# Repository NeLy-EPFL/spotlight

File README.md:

# Spotlight controller

This repository contains the control software for the Spotlight system presented in [Wang-Chen et al. (2026), Precise kinematic and muscle recording in freely behaving flies enabled by closed-loop tracking and annotation-free pose estimation
](https://go.epfl.ch/spotlight-poseforge). The firmware for the triggering microcontroller is also included.

The closed-loop control and recording programs implemented in C++. A set of offline tools for calibration, postprocessing, etc. is implemented in Python and lives in [`tools/`](tools/). The C++ codebase contains three parts:

- **`recorder/`:** The main recorder software that runs on the recording computer.
    - User-facing programs: `align-cameras`, `run-arena-registration-scan`, `run-spotlight`, and `run-homography-scan` _(planned; not yet implemented — see [`docs/configuration/camera_homography.md`](docs/configuration/camera_homography.md))_.
        - `align-cameras`: (i) _mechanically_ align the two cameras and the blue excitation light, and (ii) define a cropped ROI on each of the two muscle cameras to align the fields of view.
        - `run-arena-registration-scan`: move the translation stages to predefined positions and capture fiducial-marker snapshots, used by a Python tool to build a camera–stage–arena coordinate mapping.
        - `run-spotlight`: the main program to record experimental data.
        - `run-spotlight-headless`: `run-spotlight` without the GUI, for automated testing and performance analysis.
    - The behavior (Euresys) camera runs in-process; the two muscle (PCO) cameras run in one separate process (`pco-camera-server`) communicating over shared memory. See [`docs/architecture.md`](docs/architecture.md) for details.
- **`trigger_firmware/`**: The embedded code that runs on the triggering microcontroller.
- **`comm_protocol/`**: A lightweight JSON-based library for serial communication between the recorder and the microcontroller. Designed to be included by both sides; avoids exceptions to respect the microcontroller's linear workflow.

The repository also contains:

- **`tools/`**: Offline Python tools for calibration and postprocessing (`fit-arena-registration`, `postprocess-recording`, etc.). See `tools/README.md`.
- **`trigger_hardware/`**: KiCad schematic and PCB layout for the triggering microcontroller circuit board.

## Documentation & developer info

Documentation is available in the `docs/` folder. Start at the index,
[`docs/README.md`](docs/README.md), which splits the pages into a short **User's
manual** (running an experiment end to end) and a fuller **Developer's manual**
(internals, environment setup, hardware). A few entry points:

- [Architecture overview](docs/architecture.md): threads, cameras, and the trigger microcontroller.
- [Data acquisition workflow](docs/data_acquisition.md): how the cameras and lights are controlled and synchronized using continuous acquisition.
- [Building and installing](docs/setup/building.md) and [software dependencies](docs/setup/dependencies.md): how to build the components and install their dependencies.
- [Troubleshooting](docs/troubleshooting.md): common runtime problems (e.g. the behavior camera grabber being held by another program, and hangs on quit).

- Code style and conventions (language standards, formatting, naming, overhead, tests)
are documented in [`docs/code_style.md`](docs/code_style.md).

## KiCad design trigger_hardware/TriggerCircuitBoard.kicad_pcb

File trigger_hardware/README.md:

# Trigger circuit hardware

This folder contains the hardware design of the trigger controller.

See `TriggerCircuitBoard.pdf` for a schematic diagram of the triggering circuit. The CAD files (`.kicad_pro`, `.kicad_sch`, `.kicad_pcb`) can be opened using [KiCAD](https://www.kicad.org/).

## Bill of materials

Note: Symbols are as shown in the schematic diagram. All components are through-hole-mounted (THT), 2.54 mm pitch. Components can generally be replaced by equivalent parts. Exception: replacement of the microcontroller and the status display is possible but requires firmware code change.

| Symbol | Description | Model |
| --- | --- | --- |
| A1 | Microcontroller | Arduino Nano ESP32 |
| Q1–3 | NPN BJT transistors | Onsemi BC33725BU |
| R1–3 | ~500 Ω resistors | Vishay MBB02070C5600FCT00 |
| R4–6 | ~1 kΩ resistors | Vishay MRS16000C1001FC100 |
| D1 | RGB LED | RND 135-00191 |
| DISP1 | Display with I2C backpack | Midas MDOB128064WV-YBI |
| C1 | Polarized capacitor, ~200 μF, ≥ 24 V | Würth Elektronik 860010473011
| C2 | Non-polarized capacitor, ~100 nF, ≥ 3.3 V | Kemet μ1J63 1M2 |
| SW1 | Double pole, single throw (DPST) switch | RND 210-00549 |
| SW2 | Pushbutton | RND 210-00577 |
| J1–2 | Header pins & receptacles | Preci-Dip 890-18-036-10-804 / 3 (pins, soldered on Arduino) & 801-87-050-10-001101 (receptacles, soldered on PCB)
| J3 | 10-contact IDC connectors & cable | RS PRO 625-7252 plug (soldered on PCB), Würth Elektronik 63911015521CAB ribbon cable with RND 205-00682 socket (PCB side) and 3M 7100234235 panel-mount socket (on the exterior of the electronics box)
| J4 | 2-contact screw terminal & DC pwer connector | Phoenix Contact 2204260 screw terminal & RND 205-00909 external DC power connector |
| J5–10 | 4-contact screw terminal | Phoenix Contact 1725672 |
| J11–14 | BNC RF socket | RS PRO 546-3995 |

Additionally: Various jump wires, prototyping PCB (RS PRO 159-6322) cutout and header pins/receptacles for status display mounting, prototyping PCB cutout for GND bus.

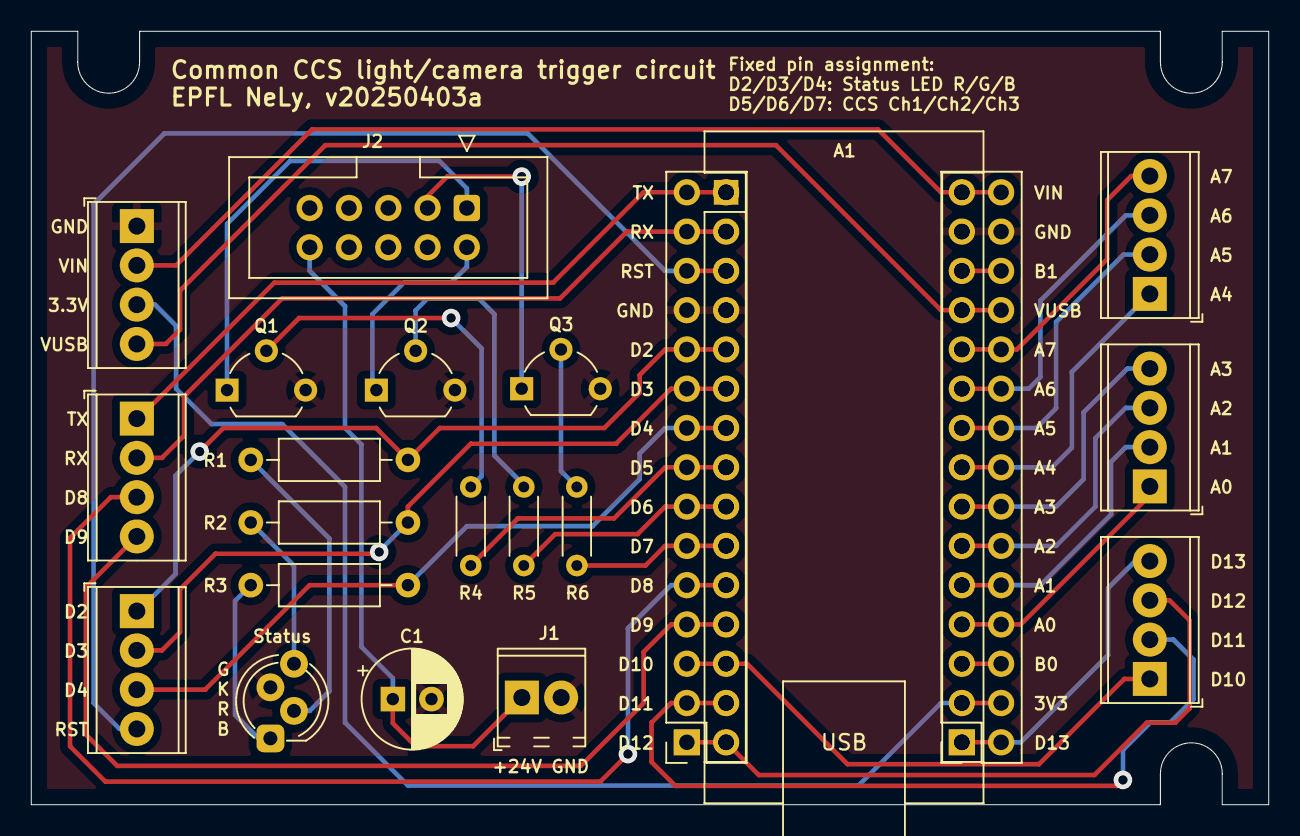
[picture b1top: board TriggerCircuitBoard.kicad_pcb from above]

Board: 2 copper layers, 80.0 x 50.0 mm, 22 parts (0 on the bottom side), 39 nets.

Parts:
A1: Arduino_Nano_ESP32; Arduino_Nano
C1: C_Polarized; CP_Radial_D6.3mm_P2.50mm
J1: Screw_Terminal_01x02; TerminalBlock_Phoenix_MPT-0,5-2-2.54_1x02_P2.54mm_Horizontal
J2: Conn_02x05_Odd_Even; IDC-Header_2x05_P2.54mm_Vertical
J4, J5, J6, J7, J8, J9: Screw_Terminal_01x04; TerminalBlock_Phoenix_MPT-0,5-4-2.54_1x04_P2.54mm_Horizontal
J10, J11: Conn_02x15_Odd_Even; PinSocket_2x15_P2.54mm_Vertical
Q1, Q2, Q3: BC337; TO-92L_Wide
R1, R2, R3: R; R_Axial_DIN0207_L6.3mm_D2.5mm_P10.16mm_Horizontal
R4, R5, R6: R; R_Axial_DIN0204_L3.6mm_D1.6mm_P5.08mm_Horizontal
Status: LED_BRKG; LED_D5.0mm-4_RGB_Staggered_Pins

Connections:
+24V: C1.1, J1.1, J2.10
/3V3: A1.17 (3V3), J5.3, J10.3, J10.4
/A0: A1.19 (A0), J8.1, J10.7, J10.8
/A1: A1.20 (A1), J8.2, J10.9, J10.10
/A2: A1.21 (A2), J8.3, J10.11, J10.12
/A3: A1.22 (A3), J8.4, J10.13, J10.14
/A4: A1.23 (SDA/A4), J9.1, J10.15, J10.16
/A5: A1.24 (SCL/A5), J9.2, J10.17, J10.18
/A6: A1.25 (A6), J9.3, J10.19, J10.20
/A7: A1.26 (A7), J9.4, J10.21, J10.22
/B0: A1.18 (B0), J10.5, J10.6
/B1: A1.28 (B1), J10.25, J10.26
/CCS_Ch1_LVTTL: A1.8 (D5), J11.15, J11.16, R4.1
/CCS_Ch1_Sink_Out: J2.1, Q1.1 (C)
/CCS_Ch2_LVTTL: A1.9 (D6), J11.13, J11.14, R5.1
/CCS_Ch2_Sink_Out: J2.2, Q2.1 (C)
/CCS_Ch3_LVTTL: A1.10 (D7), J11.11, J11.12, R6.1
/CCS_Ch3_Sink_Out: J2.3, Q3.1 (C)
/D8: A1.11 (D8), J6.3, J11.9, J11.10
/D9: A1.12 (D9), J6.4, J11.7, J11.8
/D10: A1.13 (D10/CS), J7.1, J11.5, J11.6
/D11: A1.14 (D11/COPI), J7.2, J11.3, J11.4
/D12: A1.15 (D12/CIPO), J7.3, J11.1, J11.2
/D13: A1.16 (D13/SCK), J7.4, J10.1, J10.2
/Indicator_Blue: A1.7 (D4), J4.3, J11.17, J11.18, R3.2
/Indicator_Green: A1.6 (D3), J4.2, J11.19, J11.20, R2.2
/Indicator_Red: A1.5 (D2), J4.1, J11.21, J11.22, R1.2
/RST: A1.3 (~RESET), J4.4, J11.25, J11.26
/RX: A1.2 (D0/RX), J6.2, J11.27, J11.28
/TX: A1.1 (D1/TX), J6.1, J11.29, J11.30
/VIN: A1.30 (VIN), J5.2, J10.29, J10.30
/VUSB: A1.27 (VUSB/5V), J5.4, J10.23, J10.24
GND: A1.4 (GND), A1.29 (GND), C1.2, J1.2, J5.1, J10.27, J10.28, J11.23, J11.24, Q1.3 (E), Q2.3 (E), Q3.3 (E), Status.3 (K)
unnamed: R3.1, Status.1 (BA)
unnamed: R2.1, Status.4 (GA)
unnamed: R1.1, Status.2 (RA)
unnamed: Q1.2 (B), R4.2
unnamed: Q2.2 (B), R5.2
unnamed: Q3.2 (B), R6.2

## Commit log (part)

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2025-04-30 remove redundant check in Arduino program
2025-04-30 refactor: Create helper function that configures triggering using default parameters. This function is called by both alignCameras and runCalibration
2025-04-30 Remove redundant comment
2025-05-05 Implement calibration model fitting for muscle camera
2025-05-05 refactor: Extract ArUco parameter configuration and image preprocessing into separate functions
2025-05-05 Remove redundant print
2025-05-05 fix: Return ArUco parameters in get_aruco_parameters function
2025-05-06 fix: Update percentile calculations in open_tif_image_and_normalize function
2025-05-06 fix typo in filename
2025-05-06 fix further typo
2025-05-07 Fix formatting
2025-05-08 #71 reorient muscle image before saving
2025-05-08 Fix#72 and add version compatibility check (#73)
2025-05-08 #73 Add function to write experiment parameters to metadata YAML file
2025-05-08 #73: add file format versions
2025-05-09 add version number to default config file #73
2025-05-09 fix pco-camera-server execl call in forked process: now searching through $PATH to find the executable
2025-05-09 Improve blackoutOutside code to account for possible stage misalignment
2025-05-09 blackoutOutside: simplify image copying using mask - use optimized opencv call instead of copying every pixel manually
2025-05-10 Save calibration parameters to metadata upon recording
2025-05-10 change recording_config.yaml to recorder_config.yaml for consistency
2025-05-10 Add code to warp muscle images to be consistent with behavior images #70
2025-05-12 fix: Refactor muscle image processing and add summary video generation
2025-06-09 log additional metadata
2025-06-09 fix: update calibration parameters file path for behavior camera
2025-06-10 #79: add window for setting parameters for behavior-muscle dual recording
2025-06-11 fix typo
2025-06-11 feat: enhance dual recording configuration UI with behavior-only option
2025-06-11 Implement #79 on the computer side (not Arduino)
2025-06-11 implement #79 on the Arduino side
2025-06-11 (1) set real exposure time for muscle camera, (2) avoid "muscleExposureTime"; instead stating muscleLightOnTime and muscleShutterOpenTime explicitly
2025-06-12 Attempt to implement #79 by adding a delay to muscle camera config - didn't work
2025-06-12 Undo delay added to PCO camera config
2025-06-12 Implement #79 by applying the delay from Arduino
2025-06-12 fix wrong variable names
2025-06-12 Incorporate style improvements suggested by Copilot
2025-06-12 Implement Copilot's nitpicks
2025-06-12 fix: use correct sync ratio
2025-06-12 improve comments
2025-06-12 Change "exposure time" explicitly to "light-on time" in Arduino comm protocol
2025-06-12 Implement variable naming nitpicks by Copilot
2025-06-13 simplify: number of delay cycles no longer needs to be communicated to the Arduino
2025-06-13 Add initial configuration script for Euresys grabber
2025-06-13 add checks for infinite loop in case the muscle camera never initializes
2025-06-14 [WIP] add pose estimation via SLEAP
2025-06-16 update postprocessing code to synchronize muscle with behavior images
2025-06-16 Simplify visualization code - get rid of overlays
2025-06-16 get rid of deprecated parameter "muscle_to_behavior_cycles_offset"
2025-06-17 Implement SLEAP output extraction using Tommy's sleap-utils package
2025-06-17 revert postprocessing steps that were temporarily commented out
2025-06-17 Fix dirty hardcoded example
2025-06-17 Remove unused h5py dependency
2025-06-17 Replace print statement with logging for video opening error
2025-06-17 change error logging to thrown exception in case behavior video can't be opened
2025-06-17 change hard-coded sleap model paths to a config file
2025-06-17 improve logging
2025-06-17 fix docs/type hint
2025-06-17 Add 2d pose visualization to summary video
2025-06-17 fix indexing bug
2025-06-18 Improve logging and add expected_n_frames argument as per the newest version of sleap_utils
2025-06-19 cleanup commented code
2025-06-19 remove motion stage position log file if it already exists
2025-06-19 Revert "Update recorder/src/common/trackingControl.cpp"
    This reverts commit eb87f9f05eff58569be59716bfbe25738afe051c.
2025-06-19 add mapper
2025-06-19 Move image loaders to separate module in common
2025-06-20 Implement behavior dataloader with cached cv2.VideoCapture object
2025-06-20 Fix further bug: directory should be reinitialized (and existing file removed) every time recording starts, not just when the target dir changes. Otherwise we'd have problems when the user makes anot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
2025-10-15 Add BehaviorMuscleCrossMapper for pixel coordinate transformations between behavior and muscle cameras
2025-10-15 fix missing import
2025-10-26 [Feature] Use simpler 2D pose model with only 3 keypoints, instead of Tommy's bigger model
2025-10-26 [Doc] update docstrings
2025-10-26 [Fix] fix summary video generation bug
2025-10-26 [Fix] fix import path
2025-10-26 [Feature] make muscle->behavior warping more efficient (#87)
2025-10-26 [Fix] fix bug with summary video dimension
2025-10-26 [Feature] parallelize muscle image transform
2025-10-26 [Nitpick] change postprocessing defaults
2025-10-26 Map muscle image to behavior image using a single affine transform (#87)
    * Add BehaviorMuscleCrossMapper for pixel coordinate transformations between behavior and muscle cameras
    * fix missing import
    * Use simpler 2D pose model with only 3 keypoints (#88)
    * [Feature] Use simpler 2D pose model with only 3 keypoints, instead of Tommy's bigger model
    * [Doc] update docstrings
    * [Fix] fix summary video generation bug
2025-10-27 [WIP] add behavior image alignment
2025-10-27 [Fix] fix angle calculation bug
2025-10-27 [WIP] implement alignment within postprocessing
2025-10-27 [Feature/refactor] simplify postprocessing module; perform alignment on behavior and muscle images based on SLEAP predictions
2025-10-27 [Housekeeping] update poetry.lock
2025-10-28 [Feature] reimplement visualization on aligned videos + performance optimization
2025-10-28 [Refactor] cleanup obsolete dataloaders
2025-10-28 [Doc] update docs
2025-10-28 [Nitpick] typo fix + docs improvements
2025-10-28 [Fix] change uint32 to uint64 to avoid microsecond overflow
2025-10-28 [Fix] make generate_overlay_samples conditional on with_muscle
2025-10-28 [Nitpick] clarity for verbosity
2025-10-28 Align fly and take smaller crop around it (both behavior and muscle) (#90)
    * [WIP] add behavior image alignment
    * [Fix] fix angle calculation bug
    * [WIP] implement alignment within postprocessing
    * [Refactor] improve common modules
    * [Feature/refactor] simplify postprocessing module; perform alignment on behavior and muscle images based on SLEAP predictions
    * [Housekeeping] update poetry.lock
2025-11-19 fix JAI camera ROI setting bug
2025-11-20 fix typo in roi reset
2026-01-16 Fix condition for muscle camera parameters validation
2026-03-04 add cross to behavior image for easier alignement
2026-04-28 homography calibration
2026-05-14 initial implementation of new mapping pipeline
2026-05-14 registration scan working
2026-05-18 WIP: large 146x146 mm arena with new layout
    - Removed file format version checks from various components.
    - Updated logging messages to include context in configuration loading.
    - Adjusted CLI options to require arena directory input.
    - Refactored GUI components to derive stage bounds from arena dimensions.
    - Cleaned up unused includes and files related to file format versions.
2026-05-18 Add motion control limits and update GUI to handle arena size parameters
    - Implemented methods to retrieve minimum and maximum position limits for motion control.
    - Updated motion control request handler to clamp target positions within travel limits.
    - Modified GUI components to accept arena size parameters for better visualization.
    - Adjusted related functions to ensure consistent handling of arena dimensions.
2026-05-25 wip - active area masking working, pending morph erosion
2026-05-25 fix active area masking
2026-05-26 update docs
2026-05-26 simplify readme
2026-05-26 implement software limits for motion stages
2026-05-26 apply clang-format
2026-05-26 fix include order
2026-05-26 move ActiveAreaMask class definition to trackingControl.hpp
2026-05-26 update code style
2026-05-26 change to 80 columns
2026-05-26 refactor: use const references for parameters in function signatures
2026-05-26 refactor: improve code formatting and readability in alignCameras and arduinoCommunication modules
2026-05-26 clean up .vscode/settings.json
2026-05-26 fix json syntax error
2026-05-28 wip - untested refactoring of arduino code
2026-06-01 start file structure for refactoring; implement comm protocol
2026-06-01 implement serial IO and status display
2026-06-01 Update file organization
2026-06-03 update comm protocol
2026-06-05 wip - trigger firmware
2026-06-05 rename recorder files and change file structure
2026-06-05 Remove stale tests
2026-06-06 wip - switch to new comm protocol
2026-06-06 Add enableMuscle parameter to TriggerParams and update related functionality
    - Introduced enableMuscle boolean to control muscle camera behavior in TriggerParams.
    - Updated parsing and serialization functions to handle enableMuscle.
    - Modified controller logic to support free-running and muscle-synced modes based on enableMuscle.
    - Enhanced documentation to reflect changes in data acquisition modes.
    - Updated unit tests to validate new parameter behavior.
2026-06-07 update status display for behavior-only recording
2026-06-07 wip - single GUI branch
2026-06-07 fix pco init bug
2026-06-07 common time polarity low->high
2026-06-07 wip - implement pco cam auto trigger
2026-06-07 Fix various bugs discovered by claude code: - gui: parse and validate the experiment protocol and muscle timing before any side effects (muscle exposure change, button toggles, metadata writes) so an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
2026-06-07 wip - reset upon init
2026-06-08 Add sample config files for profile and arena
2026-06-08 update default GUI parameters
2026-06-08 Update exp metadata format (time unit)
2026-06-08 improve firmware config.h clarity
2026-06-08 improve log message for invalid exp protocol
2026-06-08 make program quit more robust to error
2026-06-08 a bit of mixed refactors: 1. For scheduled recording with a protocol, stop saving frames exactly when the scheduled end is reached. 2. Remove dead code on muscle calib params 3. Refactor saver perf t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
2026-06-08 require exactly one stop at the very end of any exp protocol
2026-06-08 Working version for run-spotlight
2026-06-08 Add enable muscle imaging parameter to Arduino triggering initialization
2026-06-08 add clear log message for start/end of recording and first frame arrivals
2026-06-08 fix syntax error - extra "
2026-06-09 fix program quitting error
2026-06-09 set zaber limits upon init
2026-06-09 add contrast widget for muscle image display in GUI
2026-06-09 apply logics in Euresys setup JS script in C++ program directly
2026-06-09 refactor: add helper functions to reduce very long functions, and improve GUI layout
2026-06-09 improve docs
2026-06-09 add troubleshooting doc
2026-06-09 migrate wiki to docs/
2026-06-10 unsuccessful attempt to move pco camera server logic to the same build target as the rest of the recorder code
2026-06-10 add hardware-dependent unit tests
2026-06-10 unify docs tyle
2026-06-10 add script to reset cameras
2026-06-11 camelCase to snake_case, apply clang-format
2026-06-11 clang format: encourage const and passing-by-reference
2026-06-11 bug fixes re threading, race conditions, deadlocks, etc (see newbugs.md under this commit for details)
2026-06-11 docs and code style
2026-06-11 docs
2026-06-11 reduce status led brightness
2026-06-11 fix PAUSE logic & switch display off when paused
2026-06-12 rewrite docs
2026-06-15 add init script
2026-06-15 simplify setup script
2026-06-15 move spotlight-tools into this same repo - making it monorepo
2026-06-15 update docs & config structure for spotlight-tools
2026-06-15 add 72x48 arena and update docs
2026-06-15 update circuit design
2026-06-17 update trigger hardware
2026-06-22 update trigger circuit schematics
2026-06-23 Adding necessary points for base homography
2026-06-25 Homography working with oprhan frmes detection based on image intesity (black muscle frames)
